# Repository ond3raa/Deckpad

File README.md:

# Deckpad
This Deckpad is my first project using KiCad and Fusion 360, so I chose a simple design and set of features. I plan to use it for Discord and OBS shortcuts, or for general PC control.

##  Features

- 3D printed enclosure designed in Fusion360 and printed in a dark finish
- 128x32 OLED display for showing real-time feedback.
- EC11 Rotary Encoder for volume control and muting.
- 4x SK6812MINI-E LEDs positioned under the keys for lighting effects.
- 4 customizable keys for shortcuts.

## Inspiration

I saw the Hack Club Blueprint program on Instagram and wanted to try it. At home, I love building stuff from whatever I have around. My best projects so far are a 3-way Bluetooth speaker made from a plastic protein tub, and a turntable made from a cardboard printer box. That turntable actually placed in the top 3 for design and sound in a local competition called "Přehraj Desku 2024/25".

For this project, I wanted to do something different. I didn't want to just use "trash" or leftovers from my drawers. I wanted to use good components and make it look like a professional product. So I started my first real project: Build your own Hackpad!

## CAD
Originally, I wanted to make a special pocket for the OLED, but I ended up with a simple cutout because it looked cleaner and was easier to align.

## PCB
It connects the Seeed XIAO to all the components. It was my first time making a custom board, and I'm happy everything fits.
 
|  <br> Schematic
## BOM

- **1x** Seeed XIAO RP2040

- **1x** 0.91" OLED Display (128x32)

- **1x** EC11 Rotary Encoder (with knob)

- **4x** Mechanical Switches

- **4x** Blank DSA keycaps (White)

- **4x** SK6812MINI-E LEDs

- **1x** 3D Printed Case & Deckpad PCB

- **4x** M3x16mm screws

- **4x** M3x5x4mm heatset inserts

- **4x** Small rubber feet (anti-slip)

- **1x** USB-C Cable

## Notes
I really enjoyed moving from building things out of "trash" (like my protein tub speaker) to designing my own custom PCB and professional enclosure.

After I assemble the hardware, I plan to learn more about KMK firmware to fully customize the shortcuts for my favorite apps.

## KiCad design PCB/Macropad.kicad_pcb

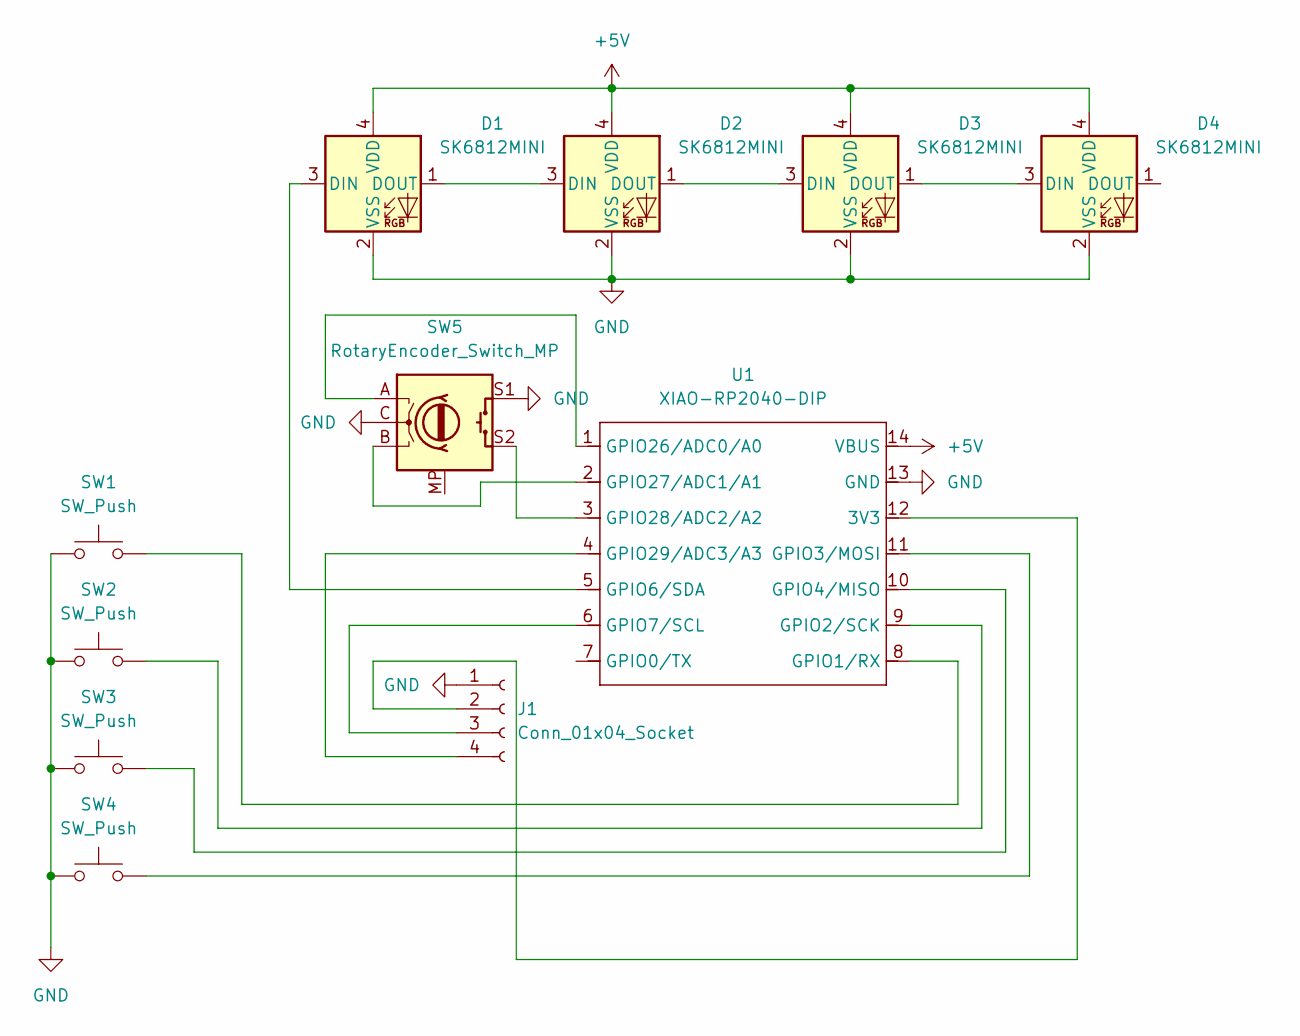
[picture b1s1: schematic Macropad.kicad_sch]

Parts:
D1, D2, D3, D4: SK6812MINI; LED_SK6812MINI_PLCC4_3.5x3.5mm_P1.75mm
J1: Conn_01x04_Socket; PinHeader_1x04_P2.54mm_Vertical
SW1, SW2, SW3, SW4: SW_Push; SW_Cherry_MX_1.00u_PCB
SW5: RotaryEncoder_Switch_MP; RotaryEncoder_Alps_EC11E-Switch_Vertical_H20mm
U1: XIAO-RP2040-DIP

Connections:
+5V: D1.4 (VDD), D2.4 (VDD), D3.4 (VDD), D4.4 (VDD), U1.14 (VBUS)
GND: D1.2 (VSS), D2.2 (VSS), D3.2 (VSS), D4.2 (VSS), J1.1, SW1.1, SW2.1, SW3.1, SW4.1, SW5.C, SW5.S1, U1.13 (GND)
unnamed: D1.3 (DIN), U1.5 (GPIO6/SDA)
unnamed: D1.1 (DOUT), D2.3 (DIN)
unnamed: D2.1 (DOUT), D3.3 (DIN)
unnamed: D3.1 (DOUT), D4.3 (DIN)
unnamed: J1.2, U1.12 (3V3)
unnamed: J1.3, U1.6 (GPIO7/SCL)
unnamed: J1.4, U1.4 (GPIO29/ADC3/A3)
unnamed: SW1.2, U1.8 (GPIO1/RX)
unnamed: SW2.2, U1.9 (GPIO2/SCK)
unnamed: SW4.2, U1.11 (GPIO3/MOSI)
unnamed: SW3.2, U1.10 (GPIO4/MISO)
unnamed: SW5.A, U1.1 (GPIO26/ADC0/A0)
unnamed: SW5.B, U1.2 (GPIO27/ADC1/A1)
unnamed: SW5.S2, U1.3 (GPIO28/ADC2/A2)

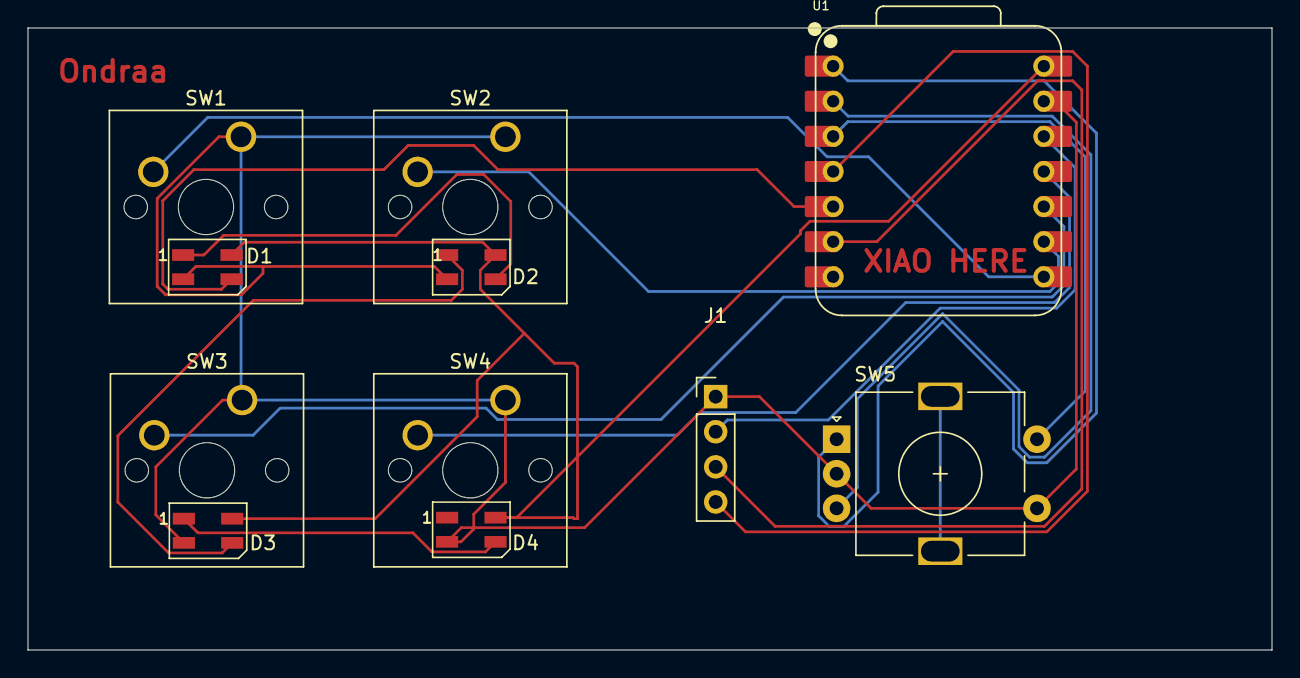
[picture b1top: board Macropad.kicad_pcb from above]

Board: 2 copper layers, 90.0 x 45.0 mm, 11 parts (0 on the bottom side), 16 nets.
